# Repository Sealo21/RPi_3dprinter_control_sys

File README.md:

# RPi_3dprinter_control_sys
Environment controller for a 3D printing enclosure using a Raspberry Pi. \
Uses a temperature/VOC sensor and a custom PCB controller for the fans and strip LEDs controlled by a Raspberry Pi. \
This project is a work-in-progress. It is functional...but still a beta.

# Components
  - Raspberry Pi 4 Model B  
  - [Sensirion Particle, VOC, Humidity, and Temperature Sensor](https://www.sparkfun.com/products/23715)  
  - [waveshare 4 inch HDMI LCD 800x480](https://www.amazon.com/gp/product/B07P5H2315/)  
  - [Geekworm GPIO Extender](https://www.amazon.com/gp/product/B0BDF48FWM/)  
  - [SamIdea 2-Pack 40pin Male to Female IDC GPIO](https://www.amazon.com/gp/product/B07CGM83QL/)  
  - [Micro HDMI Cable](https://www.sparkfun.com/products/15796)  
  - Any 2 or 4 pin PC fan [I am using Noctua NF-A8 PWM](https://noctua.at/en/nf-a8-pwm)  
  - Any SMD5050 strip LED [LED Strip Lights](https://www.amazon.com/gp/product/B08JSQVBDQ/)

# Software Installation

[Install the latest version of Raspian OS](https://projects.raspberrypi.org/en/projects/raspberry-pi-setting-up) on your Raspberry Pi \
[Edit your configuration](https://www.raspberrypi.com/documentation/computers/configuration.html) to enable 'I2C' and 'Remote GPIO' under the interfaces tab \
Save and restart your RPi 

Update packages to the latest version:
```command line
sudo apt update
```

1. Download the files marked "RPi_3dprinter_control_sys_main" 
2. Locate the file 'main' in the folder 'dist' 
3. Edit the properties of 'main' to open with the program 'Terminal' 
4. Set the permission "Execute" to 'Anyone' 
5. If you run the program without modifying these settings a pop-up may occur asking to run the executable with an application 
6. Once these settings are confirmed the program should start with a terminal followed by a window

# Hardware Setup

A GPIO Extender will be needed to have the screen and GPIO be plugged in at the same time. 

There are a few options for the hardware of your controller \
A cheap option is to breadboard the design using the design schematics from the file 'LED_FAN_CONTROLLER.kicad_sch' \
You may need to download and install Kicad to view this schematic.

Here are the design requirements to breadboard this project:
- 4 [IRL520](https://www.digikey.com/en/products/detail/vishay-siliconix/IRL520PBF/811718) Mosfets as a substitute for the [IRLL014TRPBF](https://www.digikey.com/en/products/detail/vishay-siliconix/IRLL014TRPBF/811425)
- Wire for connections
- 6 10k Ohm resistors
- 5 1k Ohm resistors
- In testing phase for 3.3V power controller for breadboarding. I have been testing using an ADALM2000
- Using [TC74HC04APF](https://www.digikey.com/en/products/detail/toshiba-semiconductor-and-storage/TC74HC04APF/870457) for PWM operations in breadboard testing

The other option is to use the PCB schematics and manufacture the PCB. \
I have not done this yet as I am working on an upgrade to the current version.

# Touchscreen

Your experience may change based on which touchscreen is used. \
Use xinput-calibrator to calibrate the touch screen. 

```
sudo apt-get install xinput-calibrator
```
You will find this program under Menu -> Preferences -> Calibrate Touchscreen. \
Follow the instuctions given in the command line to save the calibration.

If the system does not recognize the touchscreen, check with the manufacturer for driver files. 

# Installing the Sen55 Sensor

The sensors I recieved do not have a standard coloring scheme. \
I have made a table below to list where the pins must go and their color.

|  Pin (On Sensor) |  Name    |  Description    |  Color  |  Pin Placement (On RPi)  |
| ---------------- |:--------:|:-----------------:|:-------:|:------------------------:|
|  1               |  VCC     | Supply Voltage  | Green   |  Pin 2 (5V)              |
|  2               |  GND     | Ground          | Blue    |  Pin 6 (GND)             |
|  3               |  SDA     | I2C: Data       | Yellow  |  Pin 3 (SDA)             |
|  4               |  SCL     | I2C: Clock      | Black   |  Pin 5 (SCL)             |
|  5               |  SEL     | Interface Select| Red     |  Pin 9 (GND)             |
|  6               |  NC      | Do Not Connect  | Brown   |  NC                      |

If the device is not recognized by the system, connect the VCC to 3.3V pin and then back to 5V. \
The device can function on both 3.3V and 5V but 5V is recommended by the manufacturer. \
Use the i2cdetect command to check connected I2C devices.

```command line
i2cdetect -y 1
```

You should see a device listed with a number value.

More information about this installation can be found [here](https://github.com/Sensirion/raspberry-pi-i2c-sen5x)

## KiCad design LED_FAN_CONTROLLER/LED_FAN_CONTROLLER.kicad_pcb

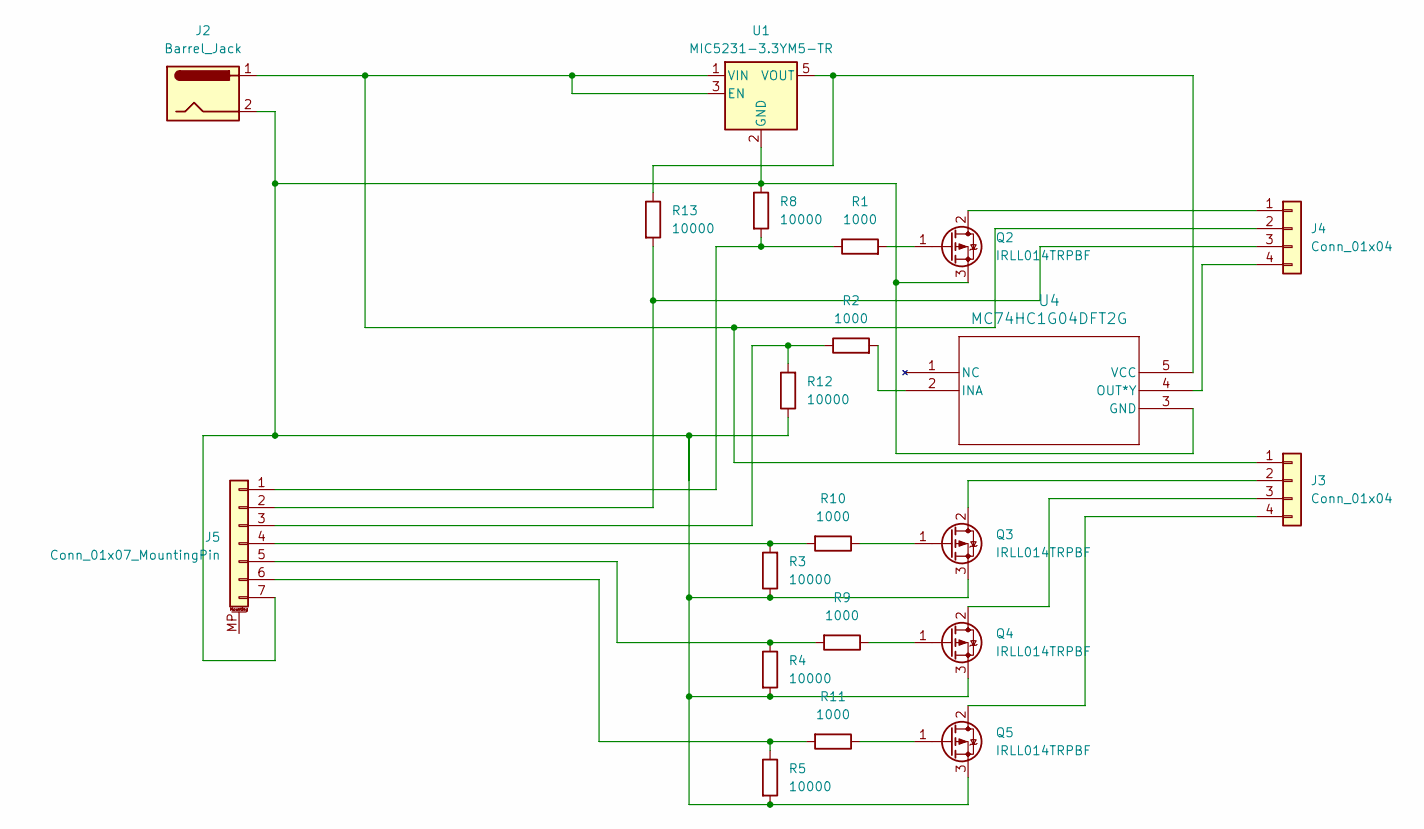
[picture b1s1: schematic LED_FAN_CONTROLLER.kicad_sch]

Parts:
J2: Barrel_Jack; BarrelJack_Horizontal
J3: Conn_01x04; PinHeader_1x04_P2.54mm_Horizontal
J4: Conn_01x04; FanPinHeader_1x04_P2.54mm_Vertical
J5: Conn_01x07_MountingPin; PinSocket_1x07_P2.54mm_Vertical
Q2, Q3, Q4, Q5: IRLL014TRPBF; SOT-223-3_TabPin2
R1, R2, R9, R10, R11: 1000; R_0603_1608Metric
R3, R4, R5, R8, R12, R13: 10000; R_0603_1608Metric
U1: MIC5231-3.3YM5-TR; SOT-23-5
U4: MC74HC1G04DFT2G; SC70-5_ONS

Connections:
unnamed: J2.1, J3.1, J4.2, U1.1 (VIN), U1.3 (EN)
unnamed: J3.2, Q3.2 (D)
unnamed: J3.3, Q4.2 (D)
unnamed: J3.4, Q5.2 (D)
unnamed: J4.1, Q2.2 (D)
unnamed 5: J4.3, J5.2, R13.2; also elsewhere on the board
unnamed 6: J4.4, U4.4 (OUT*Y); also elsewhere on the board
unnamed: J5.1, R1.1, R8.2
unnamed: J5.3, R2.1, R12.2
unnamed: J5.4, R3.2, R10.2
unnamed: J5.5, R4.1, R9.2
unnamed: J5.6, R5.1, R11.2
unnamed 12: J2.2, J5.7, Q2.3 (S), Q3.3 (S), Q4.3 (S), Q5.3 (S), R3.1, R4.2, R5.2, R8.1, R12.1, U1.2 (GND), U4.3 (GND); also elsewhere on the board
unnamed: Q2.1 (G), R1.2
unnamed: Q3.1 (G), R10.1
unnamed: Q4.1 (G), R9.1
unnamed: Q5.1 (G), R11.1
unnamed 17: R13.1, U1.5 (VOUT), U4.5 (VCC); also elsewhere on the board
unnamed: R2.2, U4.2 (INA)

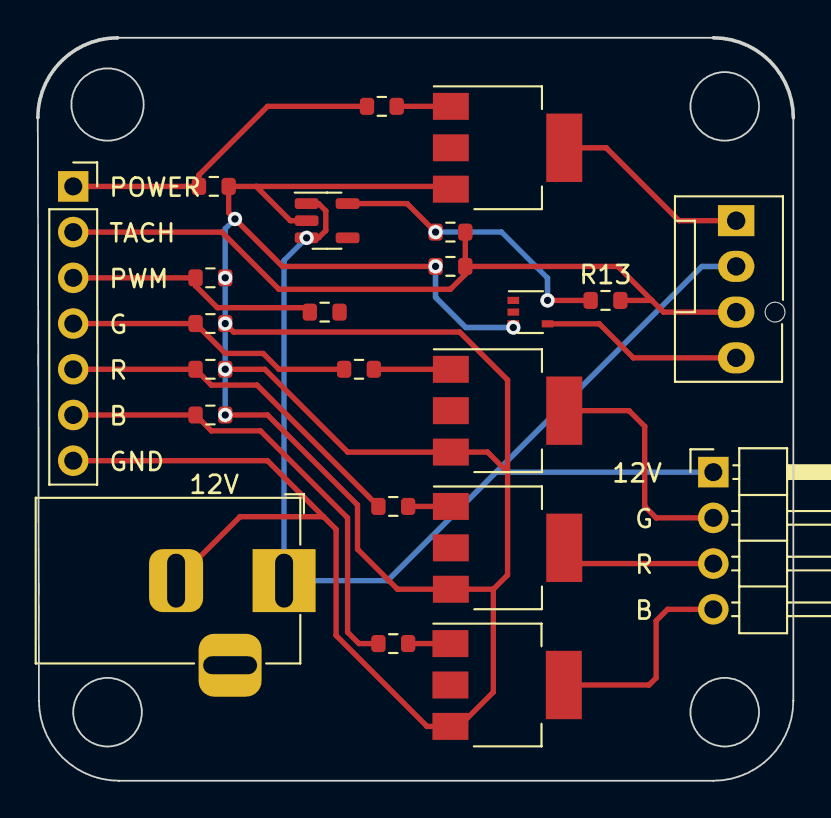
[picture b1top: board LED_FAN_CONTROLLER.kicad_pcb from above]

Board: 2 copper layers, 42.0 x 41.2 mm, 23 parts (0 on the bottom side), 18 nets.

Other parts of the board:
R6: 1700; R_0603_1608Metric
R7: 3300; R_0603_1608Metric
U2: MC74HC1G04DFT2; SOT-353_SC-70-5

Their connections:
unnamed 5: R6.1, R7.1; also elsewhere on the board
unnamed 6: U2.4 (ON); also elsewhere on the board
unnamed 12: R7.2, U2.3 (FLAGB); also elsewhere on the board
unnamed 17: R6.2, U2.5 (VIN); also elsewhere on the board
